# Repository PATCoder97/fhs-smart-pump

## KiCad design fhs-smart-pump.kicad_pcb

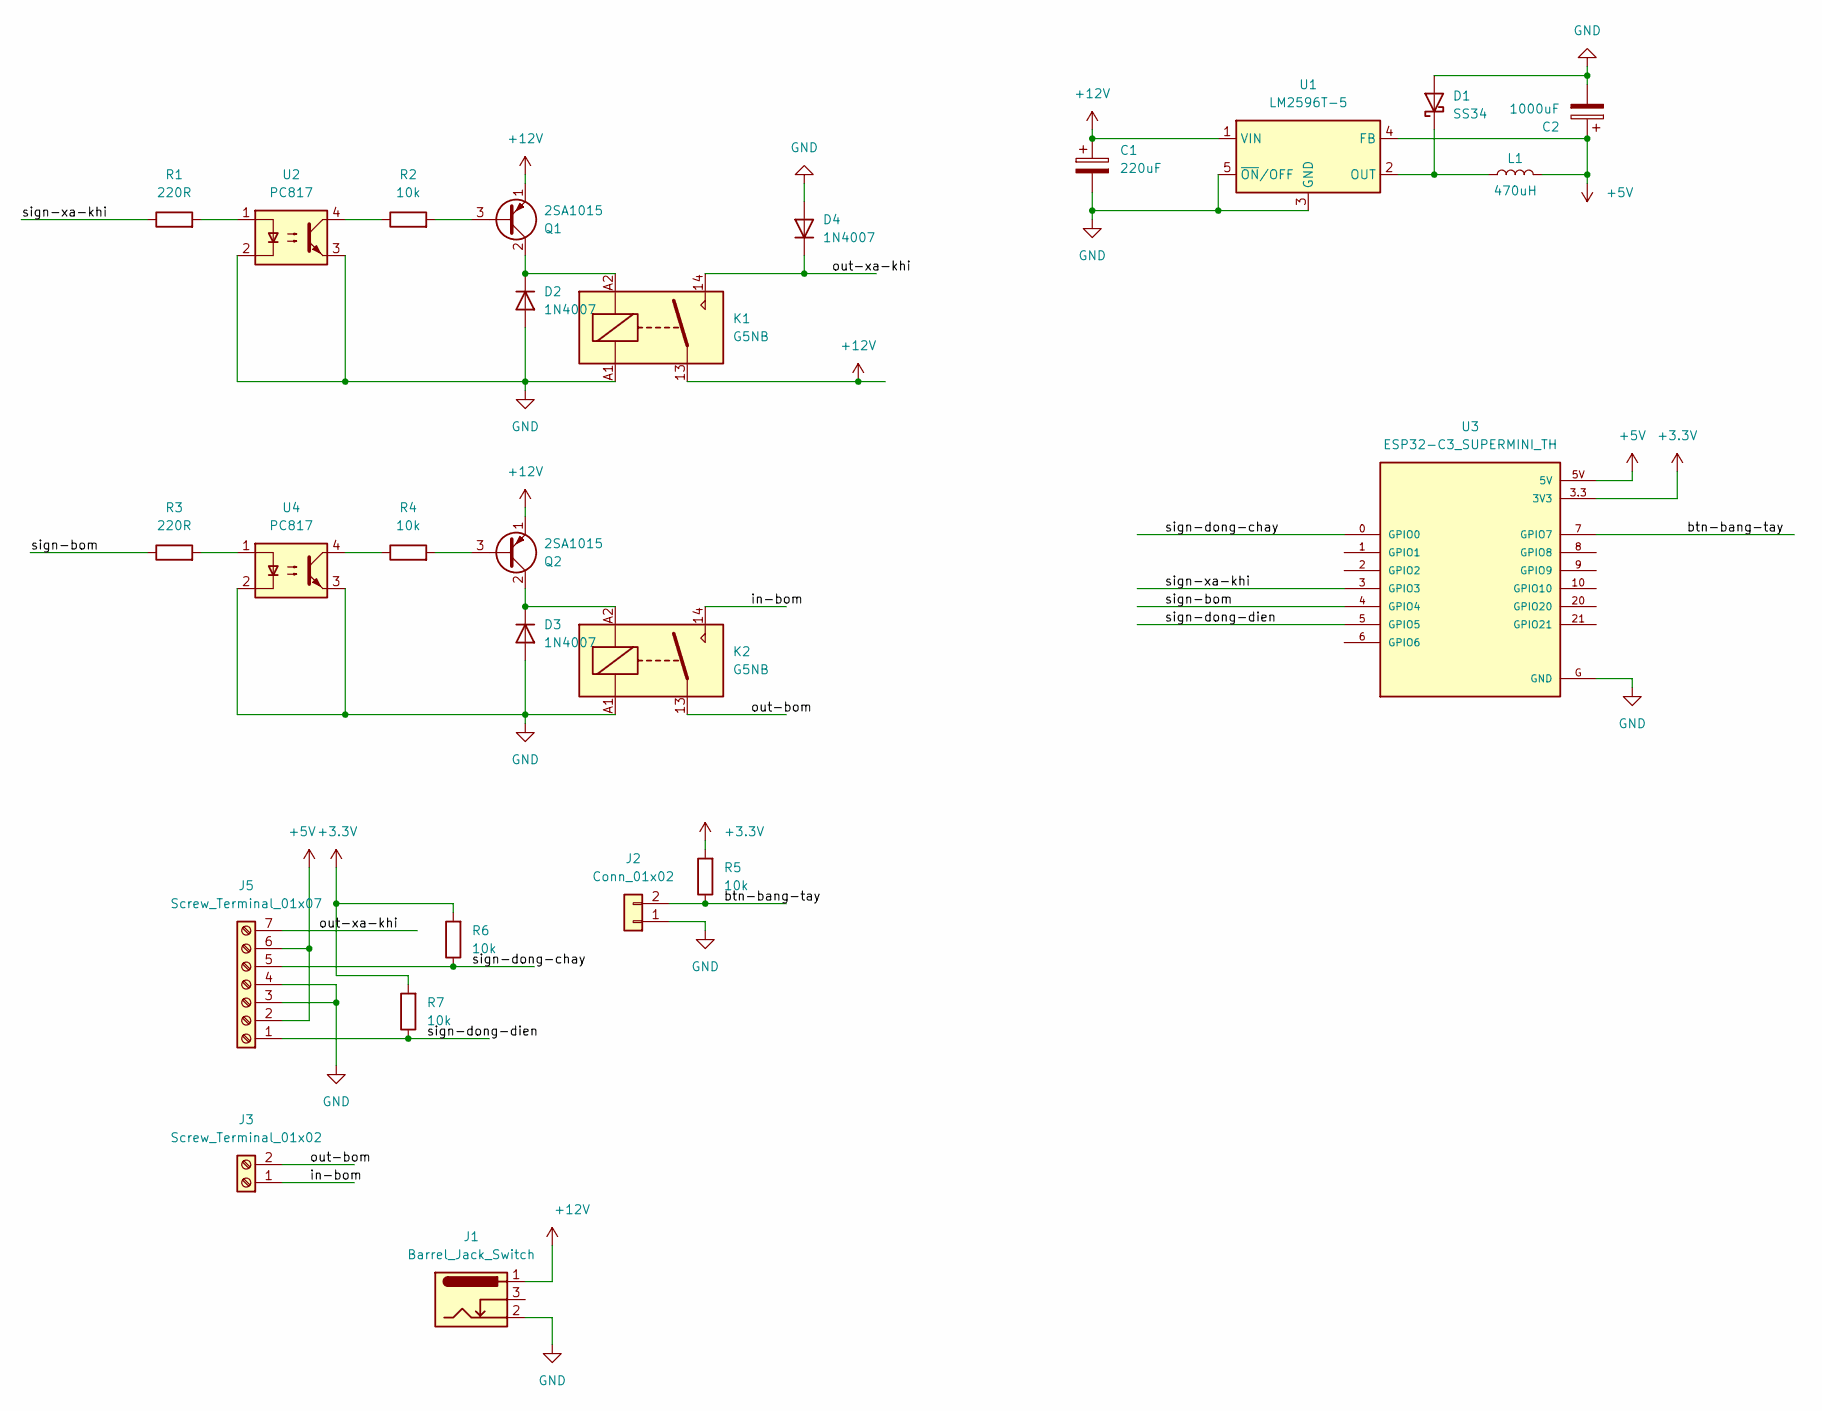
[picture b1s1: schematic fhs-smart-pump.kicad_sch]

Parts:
C1: 220uF; CP_Radial_D10.0mm_P5.00mm
C2: 1000uF; CP_Radial_D10.0mm_P5.00mm
D1: SS34; D_SMA
D2, D3: 1N4007; D_DO-41_SOD81_P7.62mm_Horizontal
D4: 1N4007; D_DO-41_SOD81_P10.16mm_Horizontal
J1: Barrel_Jack_Switch; BarrelJack_Horizontal
J2: Conn_01x02; JST_XH_B2B-XH-A_1x02_P2.50mm_Vertical
J3: Screw_Terminal_01x02; TerminalBlock_MaiXu_MX126-5.0-02P_1x02_P5.00mm
J5: Screw_Terminal_01x07; TerminalBlock_MaiXu_MX126-5.0-07P_1x07_P5.00mm
K1, K2: G5NB; Relay_SPST_Omron_G5NB
L1: 470uH; L_Radial_D12.0mm_P5.00mm_Fastron_11P
Q1, Q2: 2SA1015; TO-92_Inline_Wide
R1, R3: 220R; R_Axial_DIN0207_L6.3mm_D2.5mm_P10.16mm_Horizontal
R2, R4, R5, R6, R7: 10k; R_Axial_DIN0207_L6.3mm_D2.5mm_P10.16mm_Horizontal
U1: LM2596T-5; TO-220-5_P3.4x3.7mm_StaggerOdd_Lead3.8mm_Vertical
U2, U4: PC817; DIP-4_W7.62mm
U3: ESP32-C3_SUPERMINI_TH; MODULE_ESP32-C3_SUPERMINI_TH

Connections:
+3.3V: R5.2, R6.2, R7.2, U3.3.3 (3V3)
+5V: C2.1, J5.2, J5.6, L1.2, U1.4 (FB), U3.5V
+12V: C1.1, J1.1, K1.13, Q1.1 (E), Q2.1 (E), U1.1 (VIN)
/btn-bang-tay: J2.2, R5.1, U3.7 (GPIO7)
/in-bom: J3.1, K2.14
/out-bom: J3.2, K2.13
/out-xa-khi: D4.1 (K), J5.7, K1.14
/sign-bom: R3.1, U3.4 (GPIO4)
/sign-dong-chay: J5.5, R6.1, U3.0 (GPIO0)
/sign-dong-dien: J5.1, R7.1, U3.5 (GPIO5)
/sign-xa-khi: R1.1, U3.3 (GPIO3)
GND: C1.2, C2.2, D1.2 (A), D2.2 (A), D3.2 (A), D4.2 (A), J1.2, J2.1, J5.3, J5.4, K1.A1, K2.A1, U1.3 (GND), U1.5 (~ON/OFF), U2.2, U2.3, U3.G (GND), U4.2, U4.3
unnamed: D1.1 (K), L1.1, U1.2 (OUT)
unnamed: D2.1 (K), K1.A2, Q1.2 (C)
unnamed: D3.1 (K), K2.A2, Q2.2 (C)
unnamed: Q1.3 (B), R2.2
unnamed: Q2.3 (B), R4.2
unnamed: R1.2, U2.1
unnamed: R2.1, U2.4
unnamed: R3.2, U4.1
unnamed: R4.1, U4.4

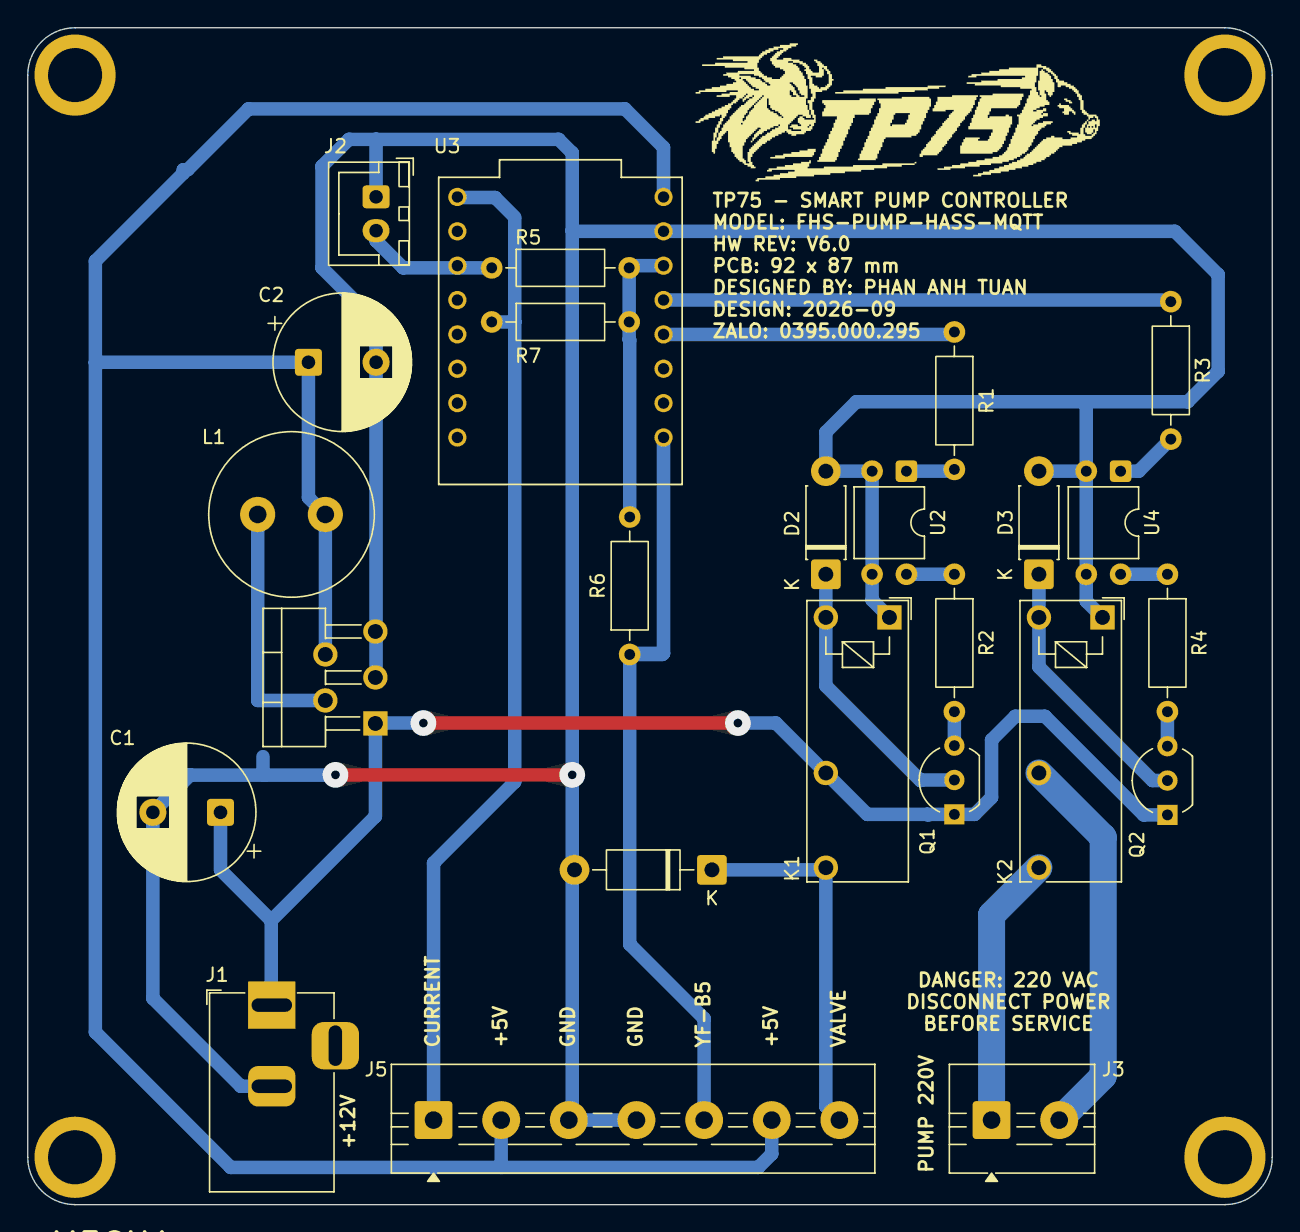
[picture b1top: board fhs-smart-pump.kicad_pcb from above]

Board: 2 copper layers, 92.0 x 87.0 mm, 27 parts (1 on the bottom side), 21 nets.

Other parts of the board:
MECH1: LK-PLC02_92x87

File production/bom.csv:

Designator,Footprint,Quantity,Value,LCSC Part #
C1,CP_Radial_D10.0mm_P5.00mm,1,220uF,
C2,CP_Radial_D10.0mm_P5.00mm,1,1000uF,
D1,D_SMA,1,SS34,
"D2, D3",D_DO-41_SOD81_P7.62mm_Horizontal,2,1N4007,
D4,D_DO-41_SOD81_P10.16mm_Horizontal,1,1N4007,
J1,TerminalBlock_MaiXu_MX126-5.0-09P_1x09_P5.00mm,1,Screw_Terminal_01x09,
J2,JST_XH_B2B-XH-A_1x02_P2.50mm_Vertical,1,Conn_01x02,
J3,TerminalBlock_MaiXu_MX126-5.0-02P_1x02_P5.00mm,1,Screw_Terminal_01x02,
"K1, K2",Relay_SPST_Omron_G5NB,2,G5NB,
L1,L_Radial_D12.0mm_P5.00mm_Fastron_11P,1,470uH,
MECH1,,1,LK-PLC02_92x87,
"Q1, Q2",TO-92_Inline_Wide,2,2SA1015,
"R1, R3",R_Axial_DIN0207_L6.3mm_D2.5mm_P10.16mm_Horizontal,2,220R,
"R2, R4, R5, R6, R7",R_Axial_DIN0207_L6.3mm_D2.5mm_P10.16mm_Horizontal,5,10k,
U1,TO-220-5_P3.4x3.7mm_StaggerOdd_Lead3.8mm_Vertical,1,LM2596T-5,
"U2, U4",DIP-4_W7.62mm,2,PC817,
U3,MODULE_ESP32-C3_SUPERMINI_TH,1,ESP32-C3_SUPERMINI_TH,
